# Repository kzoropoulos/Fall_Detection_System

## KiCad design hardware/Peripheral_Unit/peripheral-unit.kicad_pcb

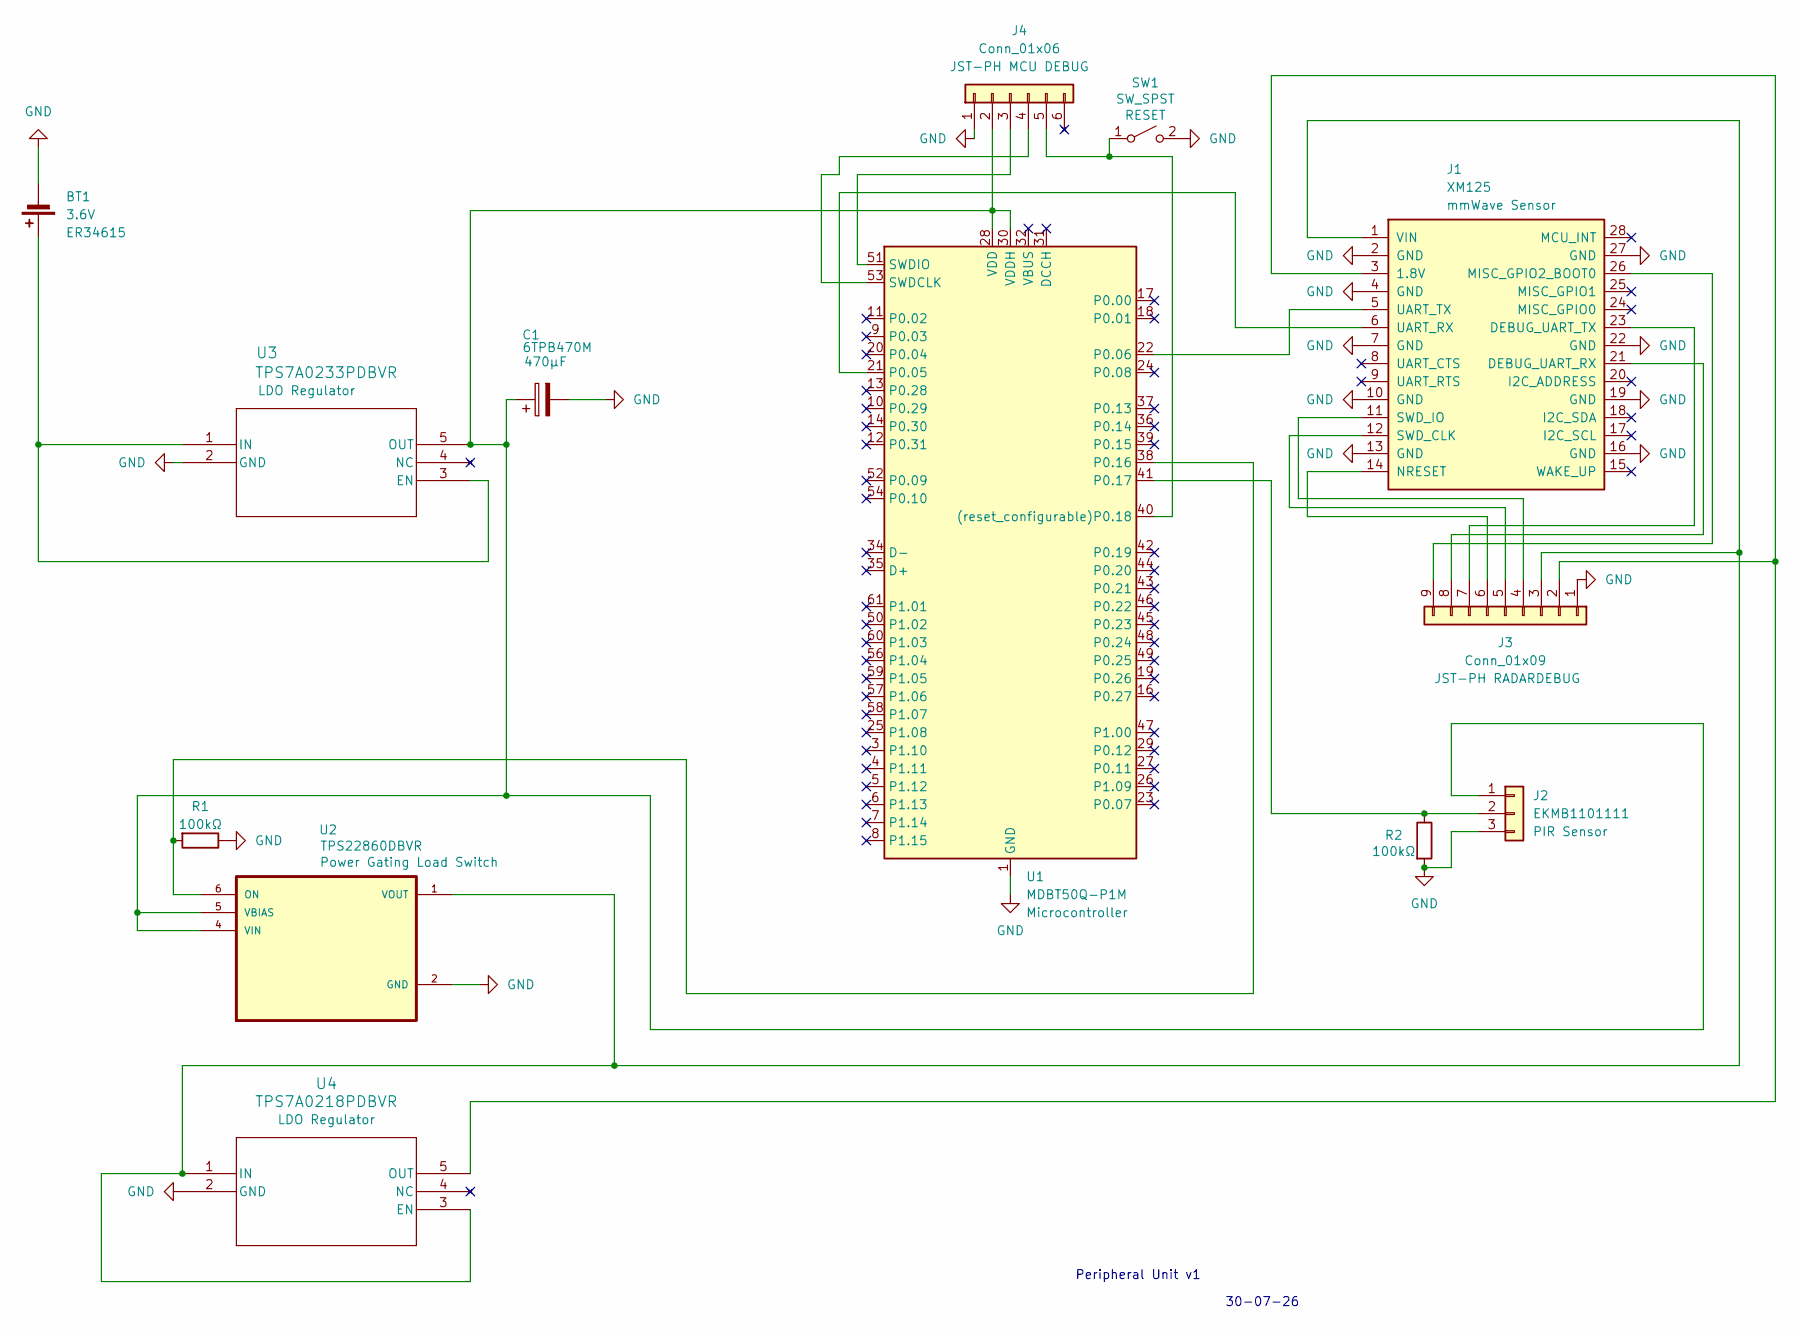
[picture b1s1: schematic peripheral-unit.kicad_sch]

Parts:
BT1: 3.6V; JST_XA_B02B-XASK-1_1x02_P2.50mm_Vertical
C1: 470μF; CP_EIA-7343-31_Kemet-D
J1: XM125
J2: EKMB1101111; EKMB 111001111
J3: Conn_01x09; JST_XA_B09B-XASK-1_1x09_P2.50mm_Vertical
J4: Conn_01x06; JST_XA_B06B-XASK-1_1x06_P2.50mm_Vertical
R1, R2: 100kΩ; R_0805_2012Metric
SW1: SW_SPST; SW_SPST_PTS810
U1: MDBT50Q-P1M; Raytac_MDBT50Q
U2: TPS22860DBVR; DBV0006A_L
U3: TPS7A0233PDBVR; SOT23_DBV_TEX
U4: TPS7A0218PDBVR; SOT23_DBV_TEX

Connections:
GND: BT1.2 (-), C1.2, J1.2 (GND), J1.4 (GND), J1.7 (GND), J1.10 (GND), J1.13 (GND), J1.16 (GND), J1.19 (GND), J1.22 (GND), J1.27 (GND), J2.3, J3.1 (GND), J4.1, R1.1, R2.2, SW1.2 (B), U1.1 (GND), U1.2 (GND), U1.15 (GND), U1.33 (GND), U1.55 (GND), U2.2 (GND), U3.2 (GND), U4.2 (GND)
unnamed: BT1.1 (+), U3.1 (IN), U3.3 (EN)
unnamed: J1.3 (1.8V), J3.2, U4.5 (OUT)
unnamed: J1.21 (DEBUG_UART_RX), J3.8
unnamed: J1.23 (DEBUG_UART_TX), J3.7
unnamed: J1.26 (MISC_GPIO2_BOOT0), J3.9
unnamed: J1.14 (NRESET), J3.6
unnamed: J1.12 (SWD_CLK), J3.5
unnamed: J1.11 (SWD_IO), J3.4
unnamed: J1.6 (UART_RX), U1.21 (P0.05)
unnamed: J1.5 (UART_TX), U1.22 (P0.06)
unnamed: J1.1 (VIN), J3.3, U2.1 (VOUT), U4.1 (IN), U4.3 (EN)
unnamed: C1.1, J2.1, J4.2, U1.28 (VDD), U1.30 (VDDH), U2.4 (VIN), U2.5 (VBIAS), U3.5 (OUT)
unnamed: J2.2, R2.1, U1.41 (P0.17)
unnamed: J4.3, U1.51 (SWDIO)
unnamed: J4.4, U1.53 (SWDCLK)
unnamed: J4.5, SW1.1 (A), U1.40 ((reset_configurable)P0.18)
unnamed: R1.2, U1.38 (P0.16), U2.6 (ON)

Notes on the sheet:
30-07-26
Peripheral Unit v1

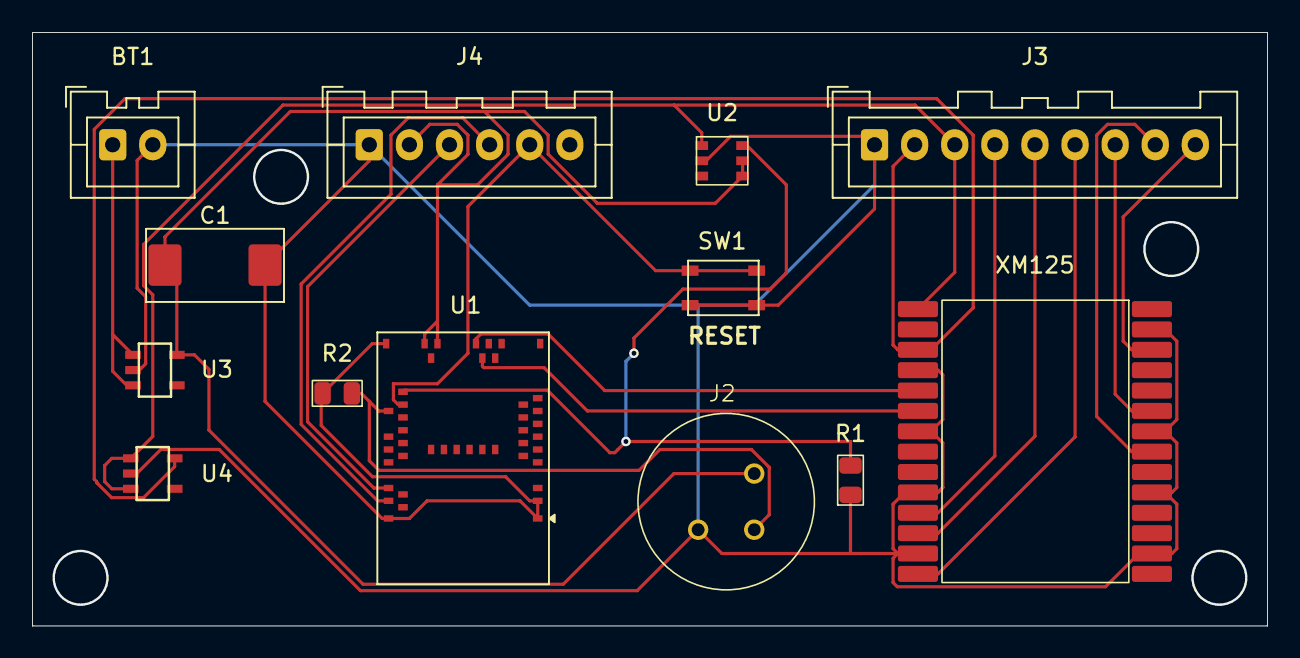
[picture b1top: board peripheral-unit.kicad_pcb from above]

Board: 2 copper layers, 77.0 x 37.0 mm, 13 parts (0 on the bottom side), 18 nets.
